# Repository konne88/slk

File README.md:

# SLK 

[Here][1]'s a post explaining how to use this code.

[1]: https://www.slkworld.com/threads/homemade-roof-operation-improvements-for-the-r171.600378

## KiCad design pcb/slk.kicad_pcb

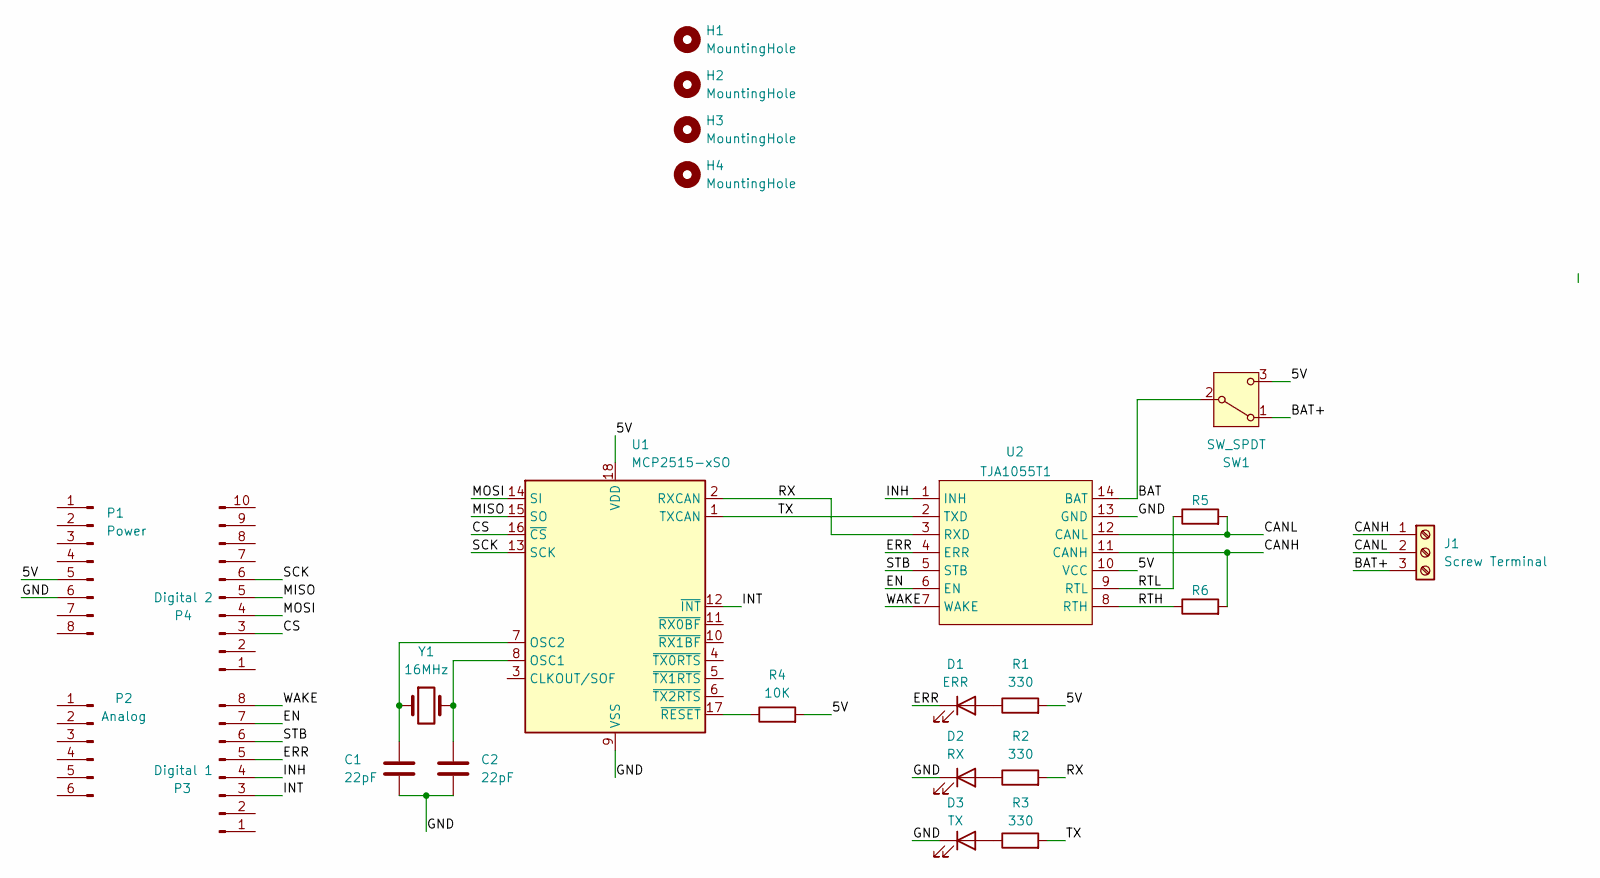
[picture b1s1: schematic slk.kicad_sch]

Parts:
C1, C2: 22pF; C_0402_1005Metric; Part Number GRM1555C1H220JA01D
D1: ERR; LED_0603_1608Metric; Part Number LTST-C190GKT
D2: RX; LED_0603_1608Metric; Part Number LTST-C191KRKT
D3: TX; LED_0603_1608Metric; Part Number LTST-C193TBKT-5A
H1, H2, H3, H4: MountingHole; MountingHole_3.2mm_M3
J1: Screw Terminal; TerminalBlock_bornier-3_P5.08mm; Part Number TERM BLK 3P SIDE ENT 5.08MM PCB
P1: Power; PinHeader_1x08_P2.54mm_Vertical; Part Number 200-SSW10803GS
P2: Analog; PinHeader_1x06_P2.54mm_Vertical; Part Number 200-SSW10603GS
P3: Digital 1; PinHeader_1x08_P2.54mm_Vertical; Part Number 200-SSW10803GS
P4: Digital 2; PinHeader_1x10_P2.54mm_Vertical; Part Number 200-SSW11003GS
R1, R2, R3: 330; R_0402_1005Metric; Part Number RC0402JR-07330RL
R4: 10K; R_0402_1005Metric; Part Number RC0402JR-0710KL
R5, R6: R; R_Axial_DIN0207_L6.3mm_D2.5mm_P7.62mm_Horizontal; Part Number Do not populate, I will hand solder thi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
SW1: SW_SPDT; SW_SPDT_CK_JS102011SAQN; Part Number JS102011SAQN
U1: MCP2515-xSO; SOIC-18W_7.5x11.6mm_P1.27mm; Part Number MCP2515T-I/SO
U2: TJA1055T1; SOIC-14_3.9x8.7mm_P1.27mm; Part Number TJA1055T/1J (935302723118)
Y1: 16MHz; Crystal_SMD_ECS_CSM3X-2Pin_7.6x4.1mm; Part Number ECS-160-20-3X-TR

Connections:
/5V: P1.5, R1.2, R4.2, SW1.3 (C), U1.18 (VDD), U2.10 (VCC)
/BAT: SW1.2 (B), U2.14 (BAT)
/BAT+: J1.3, SW1.1 (A)
/CANH: J1.1, R6.2, U2.11 (CANH)
/CANL: J1.2, R5.2, U2.12 (CANL)
/CS: P4.3, U1.16 (~CS)
/EN: P3.7, U2.6 (EN)
/ERR: D1.1 (K), P3.5, U2.4 (ERR)
/GND: C1.2, C2.2, D2.1 (K), D3.1 (K), P1.6, U1.9 (VSS), U2.13 (GND)
/INH: P3.4, U2.1 (INH)
/INT: P3.3, U1.12 (~INT)
/MISO: P4.5, U1.15 (SO)
/MOSI: P4.4, U1.14 (SI)
/RTH: R6.1, U2.8 (RTH)
/RTL: R5.1, U2.9 (RTL)
/RX: R2.2, U1.2 (RXCAN), U2.3 (RXD)
/SCK: P4.6, U1.13 (SCK)
/STB: P3.6, U2.5 (STB)
/TX: R3.2, U1.1 (TXCAN), U2.2 (TXD)
/WAKE: P3.8, U2.7 (WAKE)
unnamed: D1.2 (A), R1.1
unnamed: D2.2 (A), R2.1
unnamed: D3.2 (A), R3.1
unnamed: C2.1, U1.8 (OSC1), Y1.2
unnamed: C1.1, U1.7 (OSC2), Y1.1
unnamed: R4.1, U1.17 (~RESET)

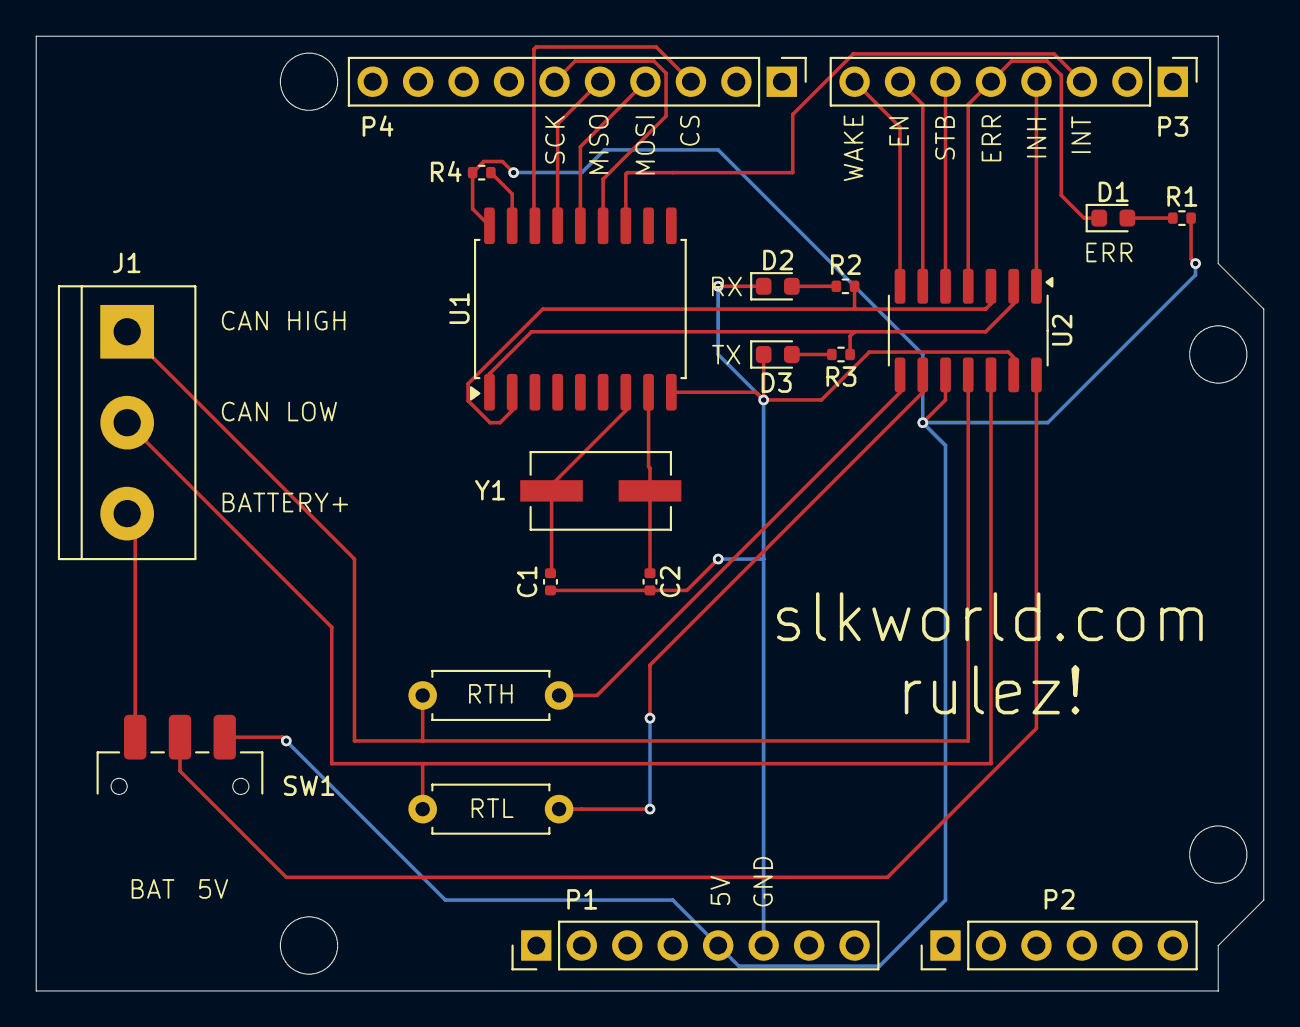
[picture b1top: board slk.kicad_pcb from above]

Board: 2 copper layers, 68.6 x 53.3 mm, 24 parts (0 on the bottom side), 26 nets.

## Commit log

2024-04-20 cleanup
2024-04-20 added replay
2024-04-20 opening the roof worksgit add -u
2024-04-21 i can open the roof
2024-04-21 open works
2024-04-21 still works
2024-04-21 it works
2024-04-21 add more debugging code
2024-04-22 recording of closing the roof with the key from standby
2024-04-28 add a recording of closing the roof with a key
2024-04-28 add pcb first draft
2024-04-28 finished schema
2024-04-28 add footprints
2024-04-28 draw board outline
2024-04-28 it should work now
2024-04-28 leds
2024-04-28 done
2024-04-29 add manual resistors
